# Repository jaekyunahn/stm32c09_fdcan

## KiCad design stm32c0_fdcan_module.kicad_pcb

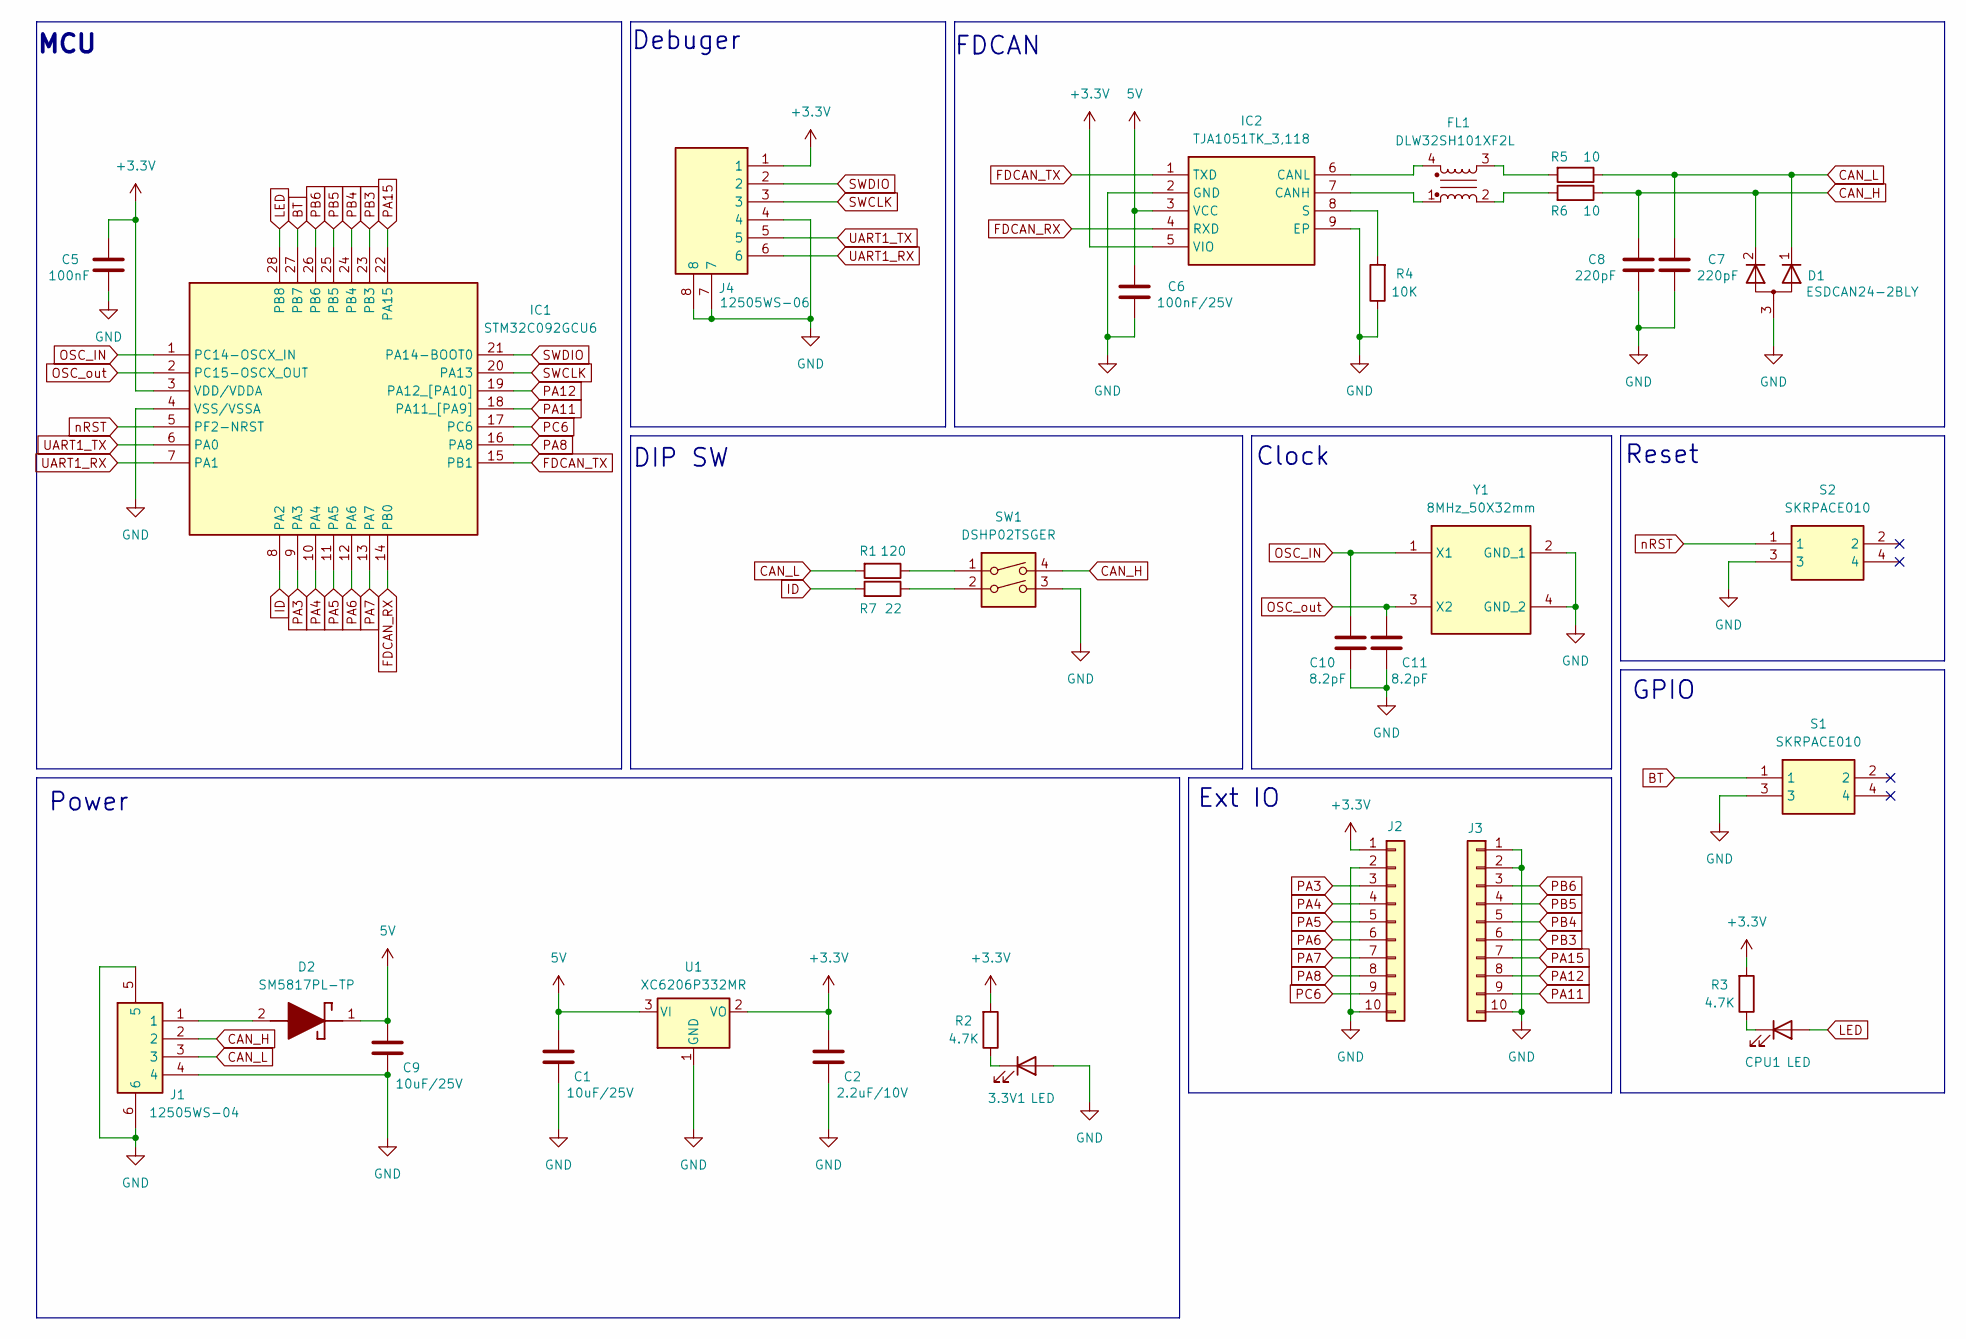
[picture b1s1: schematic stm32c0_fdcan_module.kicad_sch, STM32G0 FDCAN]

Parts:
3.3V1: LED; LED_0603_1608Metric
C1, C9: 10uF/25V; C_0805_2012Metric
C2: 2.2uF/10V; C_0805_2012Metric
C5: 100nF; C_0603_1608Metric
C6: 100nF/25V; C_0603_1608Metric
C7, C8: 220pF; C_0603_1608Metric
C10, C11: 8.2pF; C_0603_1608Metric
CPU1: LED; LED_0603_1608Metric
D1: ESDCAN24-2BLY; SOT95P255X125-3N
D2: SM5817PL-TP; SOD3716X120N; Mouser Part Number 833-SM5817PL-TP
FL1: DLW32SH101XF2L
IC1: STM32C092GCU6; QFN50P400X400X60-28N-D; Manufacturer_Part_Number STM32C051G8U6
IC2: TJA1051TK_3,118; SON65P300X300X100-9N-D; Mouser Part Number 771-TJA1051TK/3118
J1: 12505WS-04; 53261-0471; Mouser Part Number N/A
J2, J3: Conn_01x10; PinHeader_1x10_P2.54mm_Vertical
J4: 12505WS-06; 532610671; Mouser Part Number 538-53261-0471
R1: 120; R_0603_1608Metric
R2, R3: 4.7K; R_0603_1608Metric
R4: 10K; R_0603_1608Metric
R5, R6: 10; R_0603_1608Metric
R7: 22; R_0603_1608Metric
S1, S2: SKRPACE010; Mouser Part Number 688-SKRPACE010
SW1: DSHP02TSGER
U1: XC6206P332MR; SOT-23
Y1: 8MHz_50X32mm; XTAL_50X32mm; Mouser Part Number 815-ABM3C-20-D4YT

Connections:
5V: C1.1, C6.1, C9.1, D2.1 (K), IC2.3 (VCC), U1.3 (VI)
+3.3V: C2.1, C5.1, IC1.3 (VDD/VDDA), IC2.5 (VIO), J2.1, J4.1, R2.2, R3.2, U1.2 (VO)
BT: IC1.27 (PB7), S1.1
CAN_H: C8.1, D1.2 (K), J1.2, R6.1, SW1.4
CAN_L: C7.1, D1.1 (K), J1.3, R1.2, R5.1
FDCAN_RX: IC1.14 (PB0), IC2.4 (RXD)
FDCAN_TX: IC1.15 (PB1), IC2.1 (TXD)
GND: 3.3V1.2 (A), C1.2, C2.2, C5.2, C6.2, C7.2, C8.2, C9.2, C10.2, C11.2, D1.3 (A), IC1.4 (VSS/VSSA), IC2.2 (GND), IC2.9 (EP), J1.4, J1.5, J1.6, J2.2, J2.10, J3.1, J3.2, J3.10, J4.4, J4.7, J4.8, R4.1, S1.3, S2.3, SW1.3, U1.1 (GND), Y1.2 (GND_1), Y1.4 (GND_2)
ID: IC1.8 (PA2), R7.2
LED: CPU1.2 (A), IC1.28 (PB8)
unnamed: 3.3V1.1 (K), R2.1
unnamed: CPU1.1 (K), R3.1
unnamed: D2.2 (A), J1.1
unnamed: FL1.2, R6.2
unnamed: FL1.3, R5.2
unnamed: FL1.1, IC2.7 (CANH)
unnamed: FL1.4, IC2.6 (CANL)
unnamed: IC2.8 (S), R4.2
unnamed: R1.1, SW1.1
unnamed: R7.1, SW1.2
OSC_IN: C10.1, IC1.1 (PC14-OSCX_IN), Y1.1 (X1)
OSC_out: C11.1, IC1.2 (PC15-OSCX_OUT), Y1.3 (X2)
PA3: IC1.9 (PA3), J2.3
PA4: IC1.10 (PA4), J2.4
PA5: IC1.11 (PA5), J2.5
PA6: IC1.12 (PA6), J2.6
PA7: IC1.13 (PA7), J2.7
PA8: IC1.16 (PA8), J2.8
PA11: IC1.18 (PA11_[PA9]), J3.9
PA12: IC1.19 (PA12_[PA10]), J3.8
PA15: IC1.22 (PA15), J3.7
PB3: IC1.23 (PB3), J3.6
PB4: IC1.24 (PB4), J3.5
PB5: IC1.25 (PB5), J3.4
PB6: IC1.26 (PB6), J3.3
PC6: IC1.17 (PC6), J2.9
SWCLK: IC1.20 (PA13), J4.3
SWDIO: IC1.21 (PA14-BOOT0), J4.2
UART1_RX: IC1.7 (PA1), J4.6
UART1_TX: IC1.6 (PA0), J4.5
nRST: IC1.5 (PF2-NRST), S2.1

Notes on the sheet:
Ext IO
Debuger
Power
Clock
GPIO
Reset
DIP SW
FDCAN
MCU

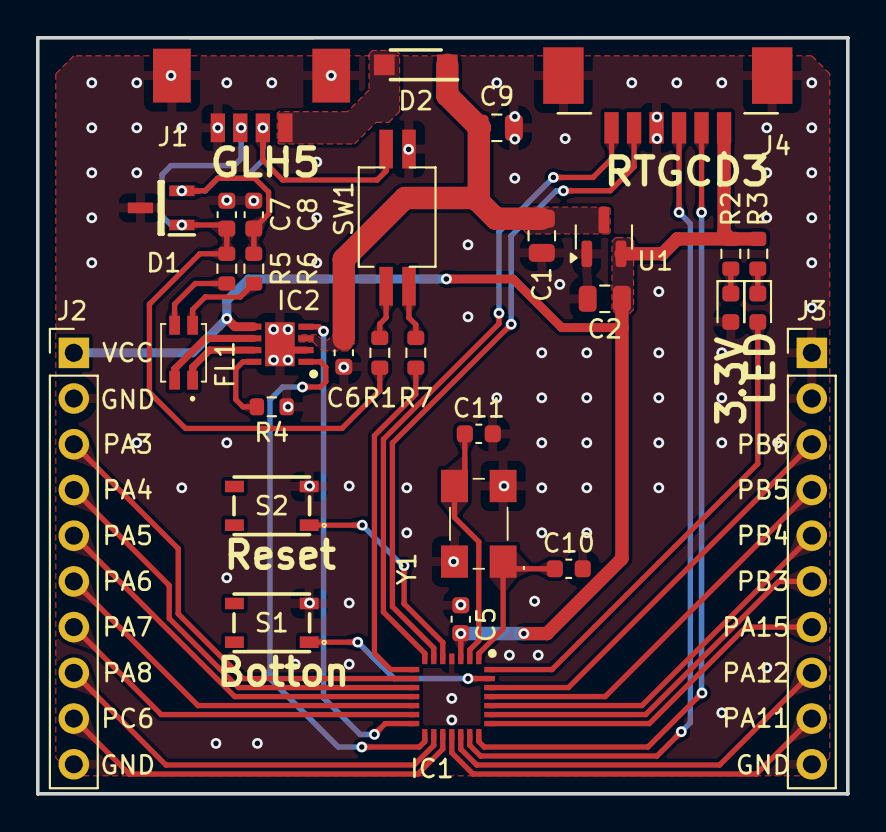
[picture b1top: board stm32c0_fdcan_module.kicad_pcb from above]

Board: 2 copper layers, 45.0 x 42.0 mm, 32 parts (0 on the bottom side), 41 nets.

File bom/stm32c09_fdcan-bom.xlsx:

Comment | Designator | Footprint | JLCPCB Part
LED | 3.3V1,CPU1 | 0603
10uF/25V | C1,C9 | 0805
2.2uF/10V | C2 | 0805
100nF | C5 | 0603
100nF/25V | C6 | 0603
220pF | C7,C8 | 0603
8.2pF | C10,C11 | 0603
ESDCAN24-2BLY | D1 | SOT95P255X125-3N
SM5817PL-TP | D2 | SOD3716X120N
DLW32SH101XF2L | FL1 | DLW32SH101XF2L
STM32C092GCU6 | IC1 | QFN50P400X400X60-28N-D
TJA1051TK_3,118 | IC2 | SON65P300X300X100-9N-D
12505WS-04 | J1 | 53261-0471:53261-0471
Conn_01x10 | J2,J3 | Connector_PinHeader_2.54mm:PinHeader_1x10_P2.54mm_Vertical
12505WS-06 | J4 | 53261-0671:532610671
120 | R1 | 0603
4.7K | R2,R3 | 0603
10K | R4 | 0603
10 | R5,R6 | 0603
22 | R7 | 0603
SKRPACE010 | S1,S2 | SKRPACE010:SKRPACE010
DSHP02TSGER | SW1 | DSHP02TSGER:DSHP02TSGER
XC6206P332MR | U1 | SOT-23
8MHz_50X32mm | Y1 | XTAL_50X32mm

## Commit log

2025-04-27 1st init
2025-05-01 단면 배치 버전
2025-05-01 EasyEDA용 압축파일 수정
2025-05-01 PCB 라우팅 수정 - 하단부 이격
2025-06-14 BOM, SMT, 거버 추가 및 일부 라우팅 수정
